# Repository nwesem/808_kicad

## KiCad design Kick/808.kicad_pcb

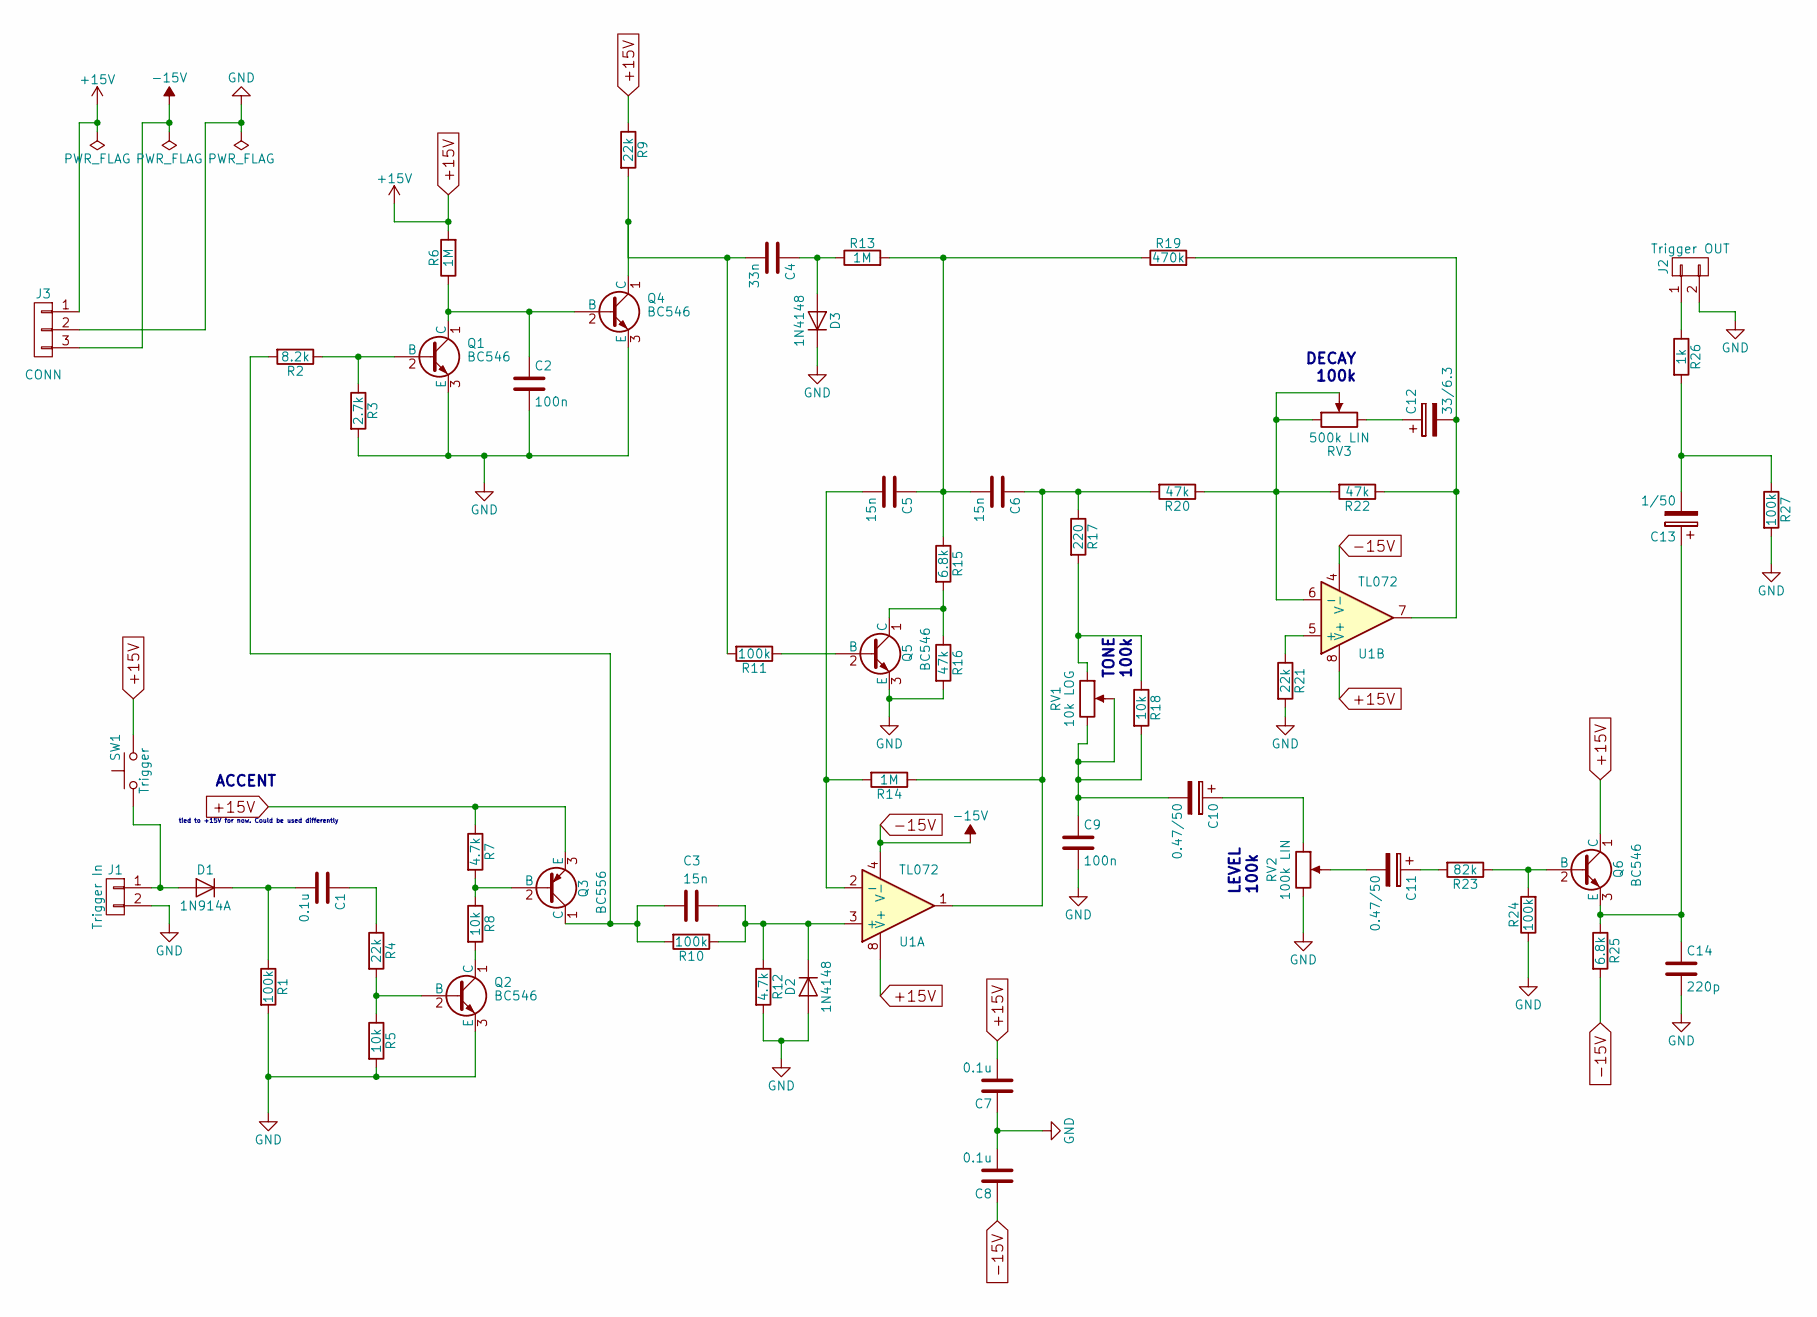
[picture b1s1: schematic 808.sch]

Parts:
C1, C7, C8: 0.1u; C_Disc_D3.0mm_W1.6mm_P2.50mm
C2, C9: 100n; C_Disc_D3.0mm_W1.6mm_P2.50mm
C3, C5, C6: 15n; C_Disc_D7.0mm_W2.5mm_P5.00mm
C4: 33n; C_Disc_D7.0mm_W2.5mm_P5.00mm
C10, C11: 0.47/50; CP_Radial_D4.0mm_P2.00mm
C12: 33/6.3; CP_Radial_D5.0mm_P2.00mm
C13: 1/50; CP_Radial_D4.0mm_P2.00mm
C14: 220p; C_Disc_D7.0mm_W2.5mm_P5.00mm
D1: 1N914A; D_A-405_P7.62mm_Horizontal
D2, D3: 1N4148; D_A-405_P7.62mm_Horizontal
J1: Trigger In; Pin_Header_Straight_1x02_Pitch2.00mm
J2: Trigger OUT; Pin_Header_Straight_1x02_Pitch2.00mm
J3: CONN; TerminalBlock_bornier-3_P5.08mm
Q1, Q2, Q4, Q5, Q6: BC546; TO-92_Molded_Narrow
Q3: BC556; TO-92_Molded_Narrow
R1, R10, R11, R24, R27: 100k; R_Axial_DIN0204_L3.6mm_D1.6mm_P5.08mm_Horizontal
R2: 8.2k; R_Axial_DIN0204_L3.6mm_D1.6mm_P5.08mm_Horizontal
R3: 2.7k; R_Axial_DIN0204_L3.6mm_D1.6mm_P5.08mm_Horizontal
R4, R9, R21: 22k; R_Axial_DIN0204_L3.6mm_D1.6mm_P5.08mm_Horizontal
R5, R8, R18: 10k; R_Axial_DIN0204_L3.6mm_D1.6mm_P5.08mm_Horizontal
R6, R13, R14: 1M; R_Axial_DIN0204_L3.6mm_D1.6mm_P5.08mm_Horizontal
R7, R12: 4.7k; R_Axial_DIN0204_L3.6mm_D1.6mm_P5.08mm_Horizontal
R15, R25: 6.8k; R_Axial_DIN0204_L3.6mm_D1.6mm_P5.08mm_Horizontal
R16, R20, R22: 47k; R_Axial_DIN0204_L3.6mm_D1.6mm_P5.08mm_Horizontal
R17: 220; R_Axial_DIN0204_L3.6mm_D1.6mm_P5.08mm_Horizontal
R19: 470k; R_Axial_DIN0204_L3.6mm_D1.6mm_P5.08mm_Horizontal
R23: 82k; R_Axial_DIN0204_L3.6mm_D1.6mm_P5.08mm_Horizontal
R26: 1k; R_Axial_DIN0204_L3.6mm_D1.6mm_P5.08mm_Horizontal
RV1: 10k LOG; Pin_Header_Straight_1x03_Pitch2.00mm
RV2: 100k LIN; Pin_Header_Straight_1x03_Pitch2.00mm
RV3: 500k LIN; Pin_Header_Straight_1x03_Pitch2.00mm
SW1: Trigger; SW_PUSH_6mm
U1: TL072; DIP-8_W7.62mm

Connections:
+15V: C7.2, J3.1, Q3.3 (E), Q6.1 (C), R6.2, R7.1, R9.1, SW1.2, U1.8 (V+)
-15V: C8.1, J3.3, R25.2, U1.4 (V-)
GND: C2.2, C7.1, C8.2, C9.2, C14.2, D2.2 (A), D3.1 (K), J1.2, J2.2, J3.2, Q1.3 (E), Q2.3 (E), Q4.3 (E), Q5.3 (E), R1.2, R3.2, R5.2, R12.2, R16.2, R21.2, R24.1, R27.2, RV2.3
unnamed: C1.1, R4.1
unnamed: C1.2, D1.1 (K), R1.1
unnamed: C2.1, Q1.1 (C), Q4.2 (B), R6.1
unnamed: C3.1, D2.1 (K), R10.1, R12.1, U1.3 (+)
unnamed: C3.2, Q3.1 (C), R2.2, R10.2
unnamed: C4.1, D3.2 (A), R13.1
unnamed: C4.2, Q4.1 (C), R9.2, R11.2
unnamed: C5.1, C6.2, R13.2, R15.1, R19.1
unnamed: C5.2, R14.2, U1.2 (-)
unnamed: C6.1, R14.1, R17.1, R20.2, U1.1
unnamed: C10.1, RV2.1
unnamed: C9.1, C10.2, R18.2, RV1.2, RV1.3
unnamed: C11.1, R23.2
unnamed: C11.2, RV2.2
unnamed: C12.1, RV3.3
unnamed: C12.2, R19.2, R22.1, U1.7
unnamed: C13.1, C14.1, Q6.3 (E), R25.1
unnamed: C13.2, R26.2, R27.1
unnamed: D1.2 (A), J1.1, SW1.1
unnamed: J2.1, R26.1
unnamed: Q1.2 (B), R2.1, R3.1
unnamed: Q2.1 (C), R8.2
unnamed: Q2.2 (B), R4.2, R5.1
unnamed: Q3.2 (B), R7.2, R8.1
unnamed: Q5.1 (C), R15.2, R16.1
unnamed: Q5.2 (B), R11.1
unnamed: Q6.2 (B), R23.1, R24.2
unnamed: R17.2, R18.1, RV1.1
unnamed: R20.1, R22.2, RV3.1, RV3.2, U1.6 (-)
unnamed: R21.1, U1.5 (+)

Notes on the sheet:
LEVEL 100k
TONE 100k
DECAY 100k
ACCENT
tied to +15V for now. Could be used differently

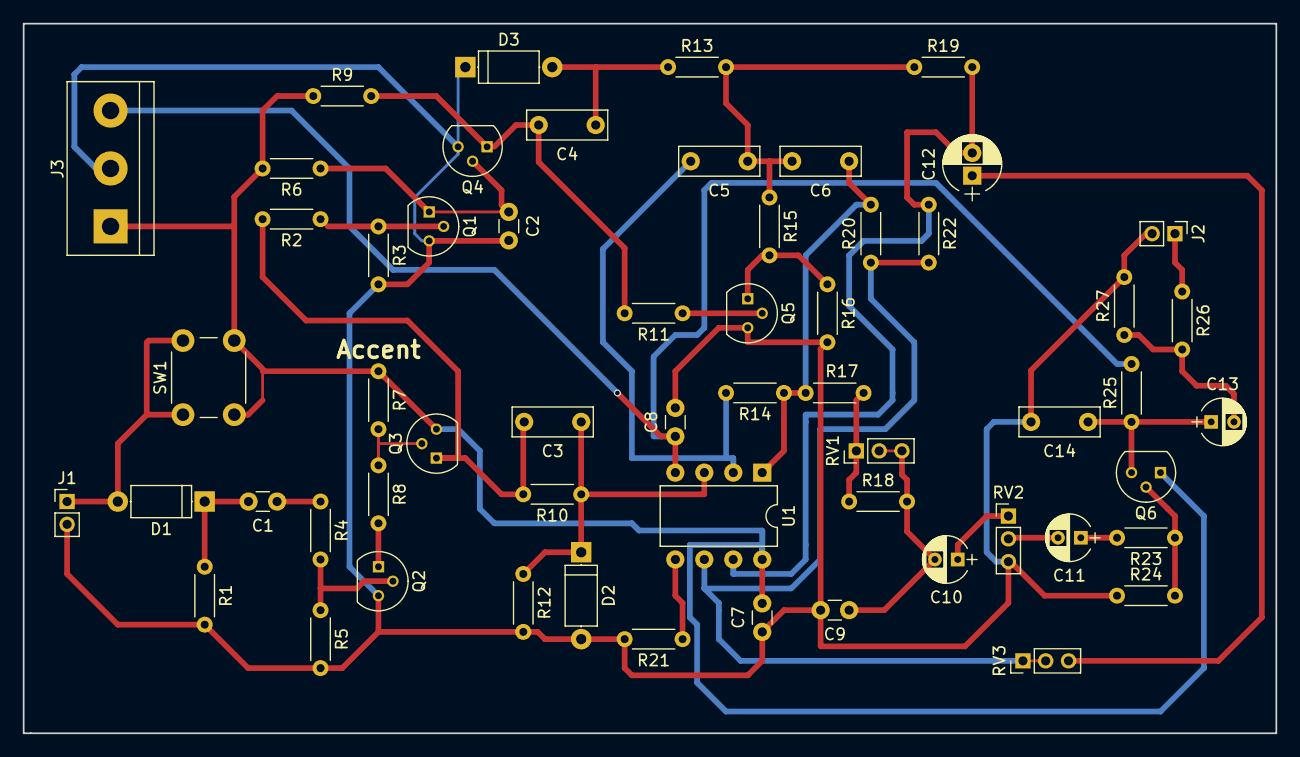
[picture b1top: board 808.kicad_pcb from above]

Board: 2 copper layers, 109.9 x 62.2 mm, 58 parts (0 on the bottom side), 33 nets.

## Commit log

2018-03-24 initial version
2018-03-25 Added one of the potis, and some power symbols.
2018-03-25 added snare scheme
2018-03-25 added folders
2018-03-25 added pwr flags to snare
2018-03-29 kick almost done
2018-03-30 kick done with higher track width
